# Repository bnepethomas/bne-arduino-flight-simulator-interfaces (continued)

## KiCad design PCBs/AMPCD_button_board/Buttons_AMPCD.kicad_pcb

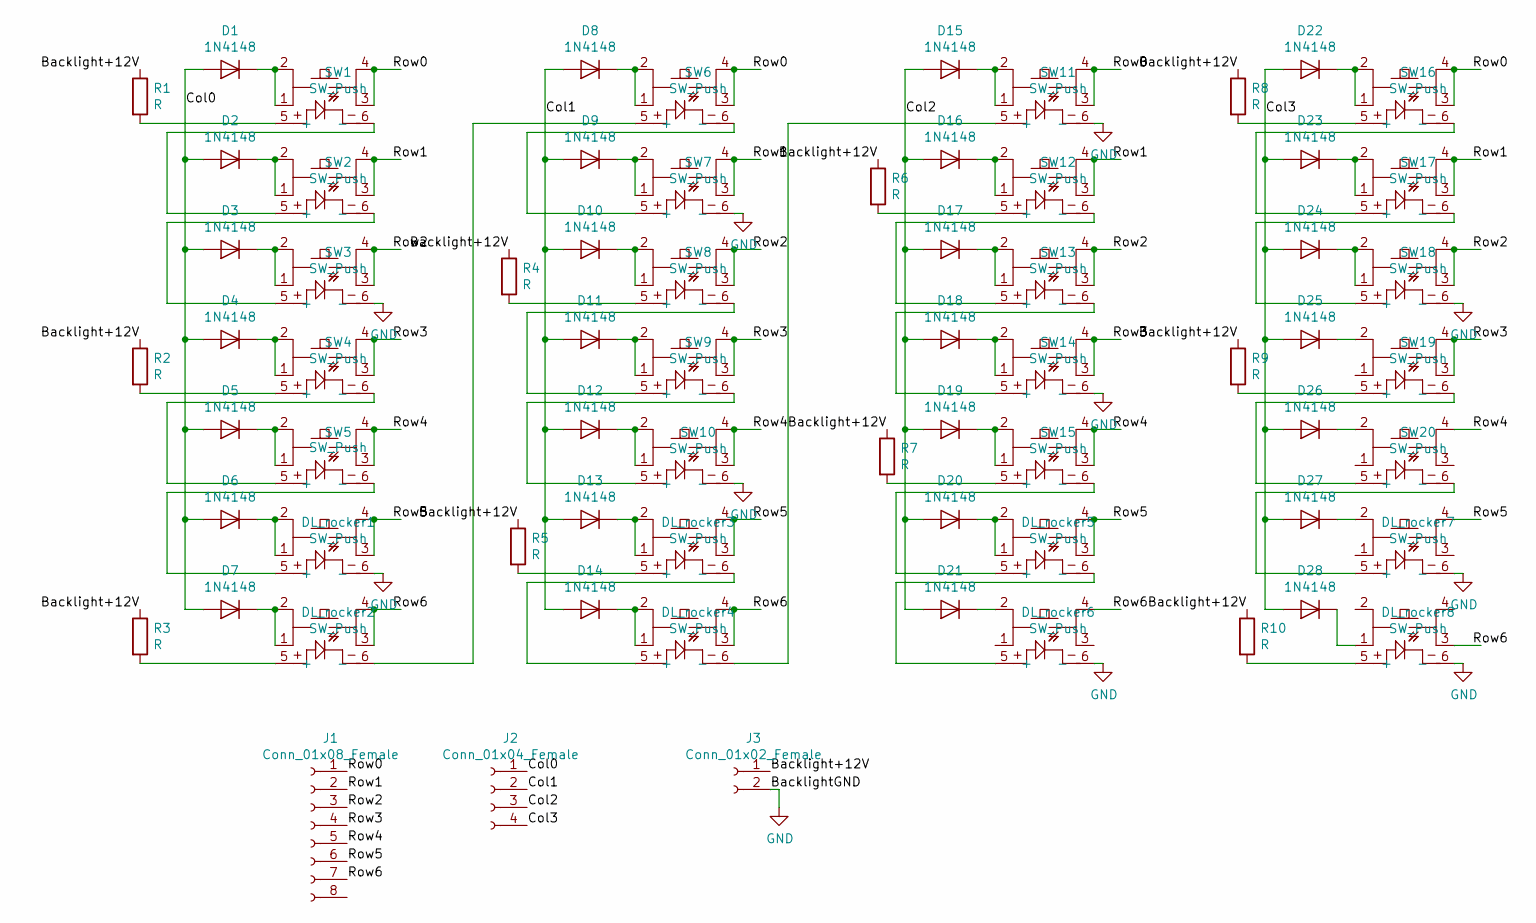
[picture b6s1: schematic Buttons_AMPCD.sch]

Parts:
D1, D2, D3, D4, D5, D6, D7, D8, D9, D10, D11, D12, D13, D14, D15, D16, D17, D18, D19, D20, D21, D22, D23, D24, D25, D26, D27, D28: 1N4148; D_DO-35_SOD27_P7.62mm_Horizontal
DL_rocker1, DL_rocker2, DL_rocker3, DL_rocker4, DL_rocker5, DL_rocker6, DL_rocker7, DL_rocker8: SW_Push; PT_Small_Tactile_Switch_With_LED
J1: Conn_01x08_Female; Molex_1x08_P2.54mm_Vertical
J2: Conn_01x04_Female; Molex_1x04_P2.54mm_Vertical
J3: Conn_01x02_Female; Molex_1x02_P2.54mm_Vertical
R1, R2, R3, R4, R5, R6, R7, R8, R9, R10: R; R_Axial_DIN0207_L6.3mm_D2.5mm_P7.62mm_Horizontal
SW1, SW2, SW3, SW4, SW5, SW6, SW7, SW8, SW9, SW10, SW11, SW12, SW13, SW14, SW15, SW16, SW17, SW18, SW19, SW20: SW_Push; PT_Small_Tactile_Switch_With_LED

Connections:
/Backlight+12V: J3.1, R1.1, R2.1, R3.1, R4.1, R5.1, R6.1, R7.1, R8.1, R9.1, R10.1
/Col0: D1.2 (A), D2.2 (A), D3.2 (A), D4.2 (A), D5.2 (A), D6.2 (A), D7.2 (A), J2.1
/Col1: D8.2 (A), D9.2 (A), D10.2 (A), D11.2 (A), D12.2 (A), D13.2 (A), D14.2 (A), J2.2
/Col2: D15.2 (A), D16.2 (A), D17.2 (A), D18.2 (A), D19.2 (A), D20.2 (A), D21.2 (A), J2.3
/Col3: D22.2 (A), D23.2 (A), D24.2 (A), D25.2 (A), D26.2 (A), D27.2 (A), D28.2 (A), J2.4
/Row0: J1.1, SW1.3, SW1.4, SW6.3, SW6.4, SW11.3, SW11.4, SW16.3, SW16.4
/Row1: J1.2, SW2.3, SW2.4, SW7.3, SW7.4, SW12.3, SW12.4, SW17.3, SW17.4
/Row2: J1.3, SW3.3, SW3.4, SW8.3, SW8.4, SW13.3, SW13.4, SW18.3, SW18.4
/Row3: J1.4, SW4.3, SW4.4, SW9.3, SW9.4, SW14.3, SW14.4, SW19.3, SW19.4
/Row4: J1.5, SW5.3, SW5.4, SW10.3, SW10.4, SW15.3, SW15.4, SW20.4
/Row5: DL_rocker1.3, DL_rocker1.4, DL_rocker3.3, DL_rocker3.4, DL_rocker5.3, DL_rocker5.4, DL_rocker7.4, J1.6
/Row6: DL_rocker2.3, DL_rocker2.4, DL_rocker4.3, DL_rocker4.4, DL_rocker6.4, DL_rocker8.3, J1.7
GND: DL_rocker1.6 (-), DL_rocker6.6 (-), DL_rocker7.6 (-), DL_rocker8.6 (-), J3.2, SW3.6 (-), SW7.6 (-), SW10.6 (-), SW11.6 (-), SW14.6 (-), SW18.6 (-)
unnamed: D1.1 (K), SW1.1, SW1.2
unnamed: D2.1 (K), SW2.1, SW2.2
unnamed: D3.1 (K), SW3.1, SW3.2
unnamed: D4.1 (K), SW4.1, SW4.2
unnamed: D5.1 (K), SW5.1, SW5.2
unnamed: D6.1 (K), DL_rocker1.1, DL_rocker1.2
unnamed: D7.1 (K), DL_rocker2.1, DL_rocker2.2
unnamed: D8.1 (K), SW6.1, SW6.2
unnamed: D9.1 (K), SW7.1, SW7.2
unnamed: D10.1 (K), SW8.1, SW8.2
unnamed: D11.1 (K), SW9.1, SW9.2
unnamed: D12.1 (K), SW10.1, SW10.2
unnamed: D13.1 (K), DL_rocker3.1, DL_rocker3.2
unnamed: D14.1 (K), DL_rocker4.1, DL_rocker4.2
unnamed: D15.1 (K), SW11.1, SW11.2
unnamed: D16.1 (K), SW12.1, SW12.2
unnamed: D17.1 (K), SW13.1, SW13.2
unnamed: D18.1 (K), SW14.1, SW14.2
unnamed: D19.1 (K), SW15.1, SW15.2
unnamed: D20.1 (K), DL_rocker5.1, DL_rocker5.2
unnamed: D21.1 (K), DL_rocker6.2
unnamed: D22.1 (K), SW16.1, SW16.2
unnamed: D23.1 (K), SW17.1, SW17.2
unnamed: D24.1 (K), SW18.1, SW18.2
unnamed: D25.1 (K), SW19.2
unnamed: D26.1 (K), SW20.2
unnamed: D27.1 (K), DL_rocker7.2
unnamed: D28.1 (K), DL_rocker8.1
unnamed: DL_rocker1.5 (+), SW5.6 (-)
unnamed: DL_rocker2.5 (+), R3.2
unnamed: DL_rocker2.6 (-), SW6.5 (+)
unnamed: DL_rocker3.5 (+), R5.2
unnamed: DL_rocker3.6 (-), DL_rocker4.5 (+)
unnamed: DL_rocker4.6 (-), SW11.5 (+)
unnamed: DL_rocker5.5 (+), SW15.6 (-)
unnamed: DL_rocker5.6 (-), DL_rocker6.5 (+)
unnamed: DL_rocker7.5 (+), SW20.6 (-)
unnamed: DL_rocker8.5 (+), R10.2
unnamed: R1.2, SW1.5 (+)
unnamed: R2.2, SW4.5 (+)
unnamed: R4.2, SW8.5 (+)
unnamed: R6.2, SW12.5 (+)
unnamed: R7.2, SW15.5 (+)
unnamed: R8.2, SW16.5 (+)
unnamed: R9.2, SW19.5 (+)
unnamed: SW1.6 (-), SW2.5 (+)
unnamed: SW2.6 (-), SW3.5 (+)
unnamed: SW4.6 (-), SW5.5 (+)
unnamed: SW6.6 (-), SW7.5 (+)
unnamed: SW8.6 (-), SW9.5 (+)
unnamed: SW9.6 (-), SW10.5 (+)
unnamed: SW12.6 (-), SW13.5 (+)
unnamed: SW13.6 (-), SW14.5 (+)
unnamed: SW16.6 (-), SW17.5 (+)
unnamed: SW17.6 (-), SW18.5 (+)
unnamed: SW19.6 (-), SW20.5 (+)

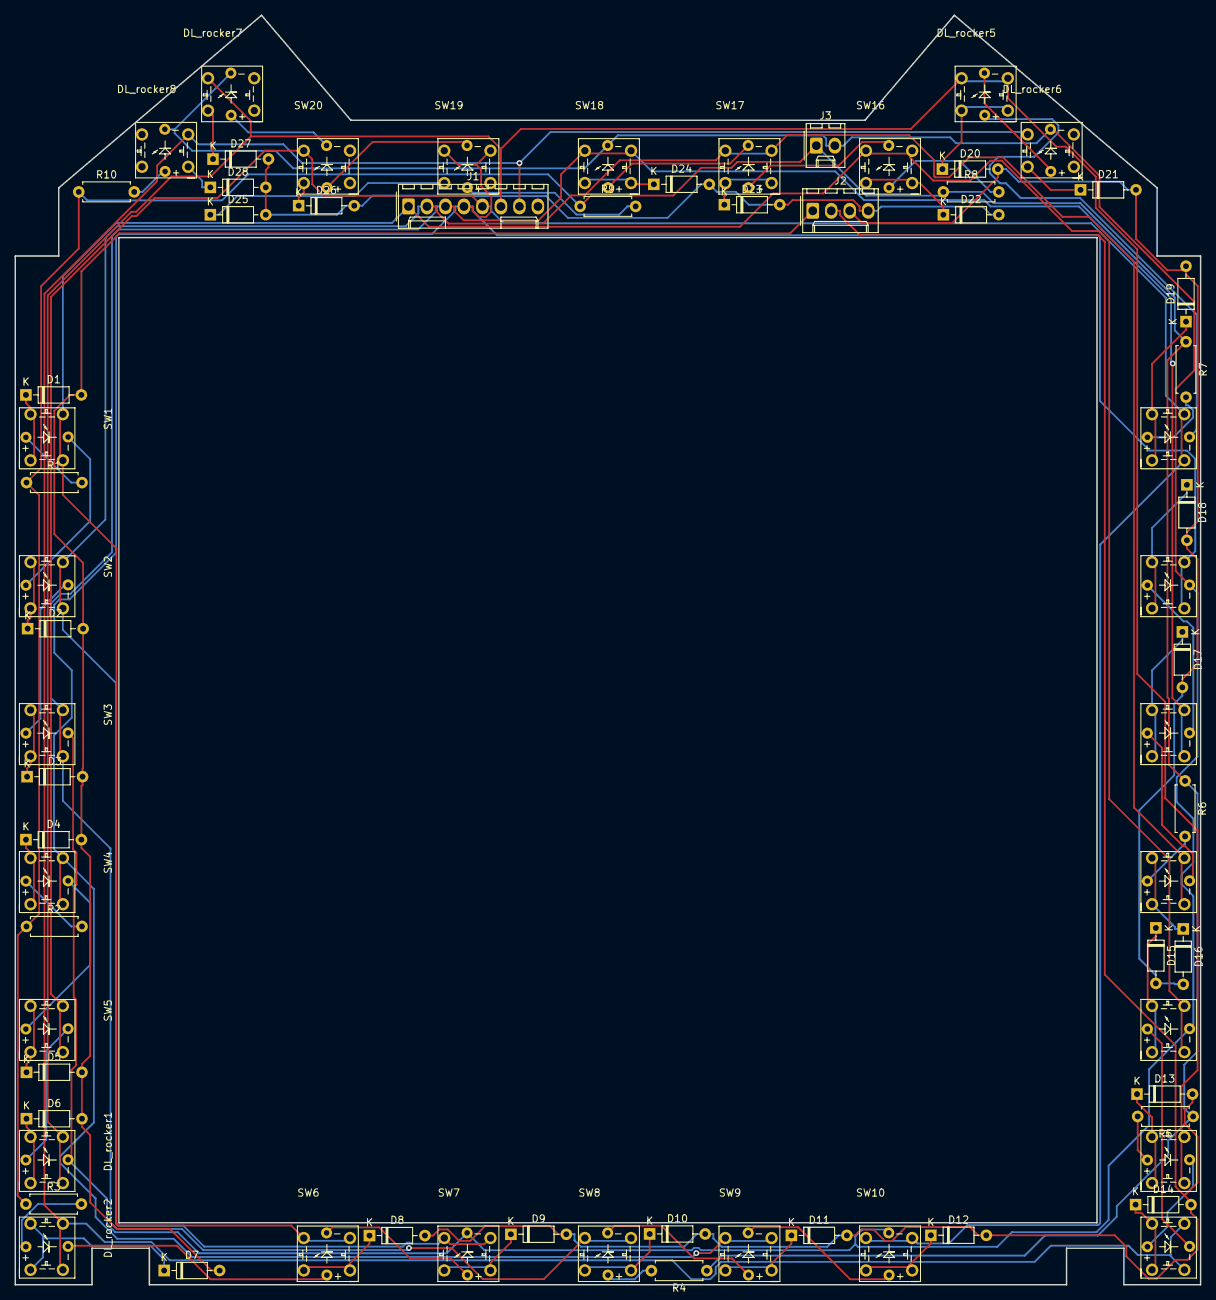
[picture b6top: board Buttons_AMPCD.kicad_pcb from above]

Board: 2 copper layers, 162.8 x 174.4 mm, 69 parts (0 on the bottom side), 69 nets.
